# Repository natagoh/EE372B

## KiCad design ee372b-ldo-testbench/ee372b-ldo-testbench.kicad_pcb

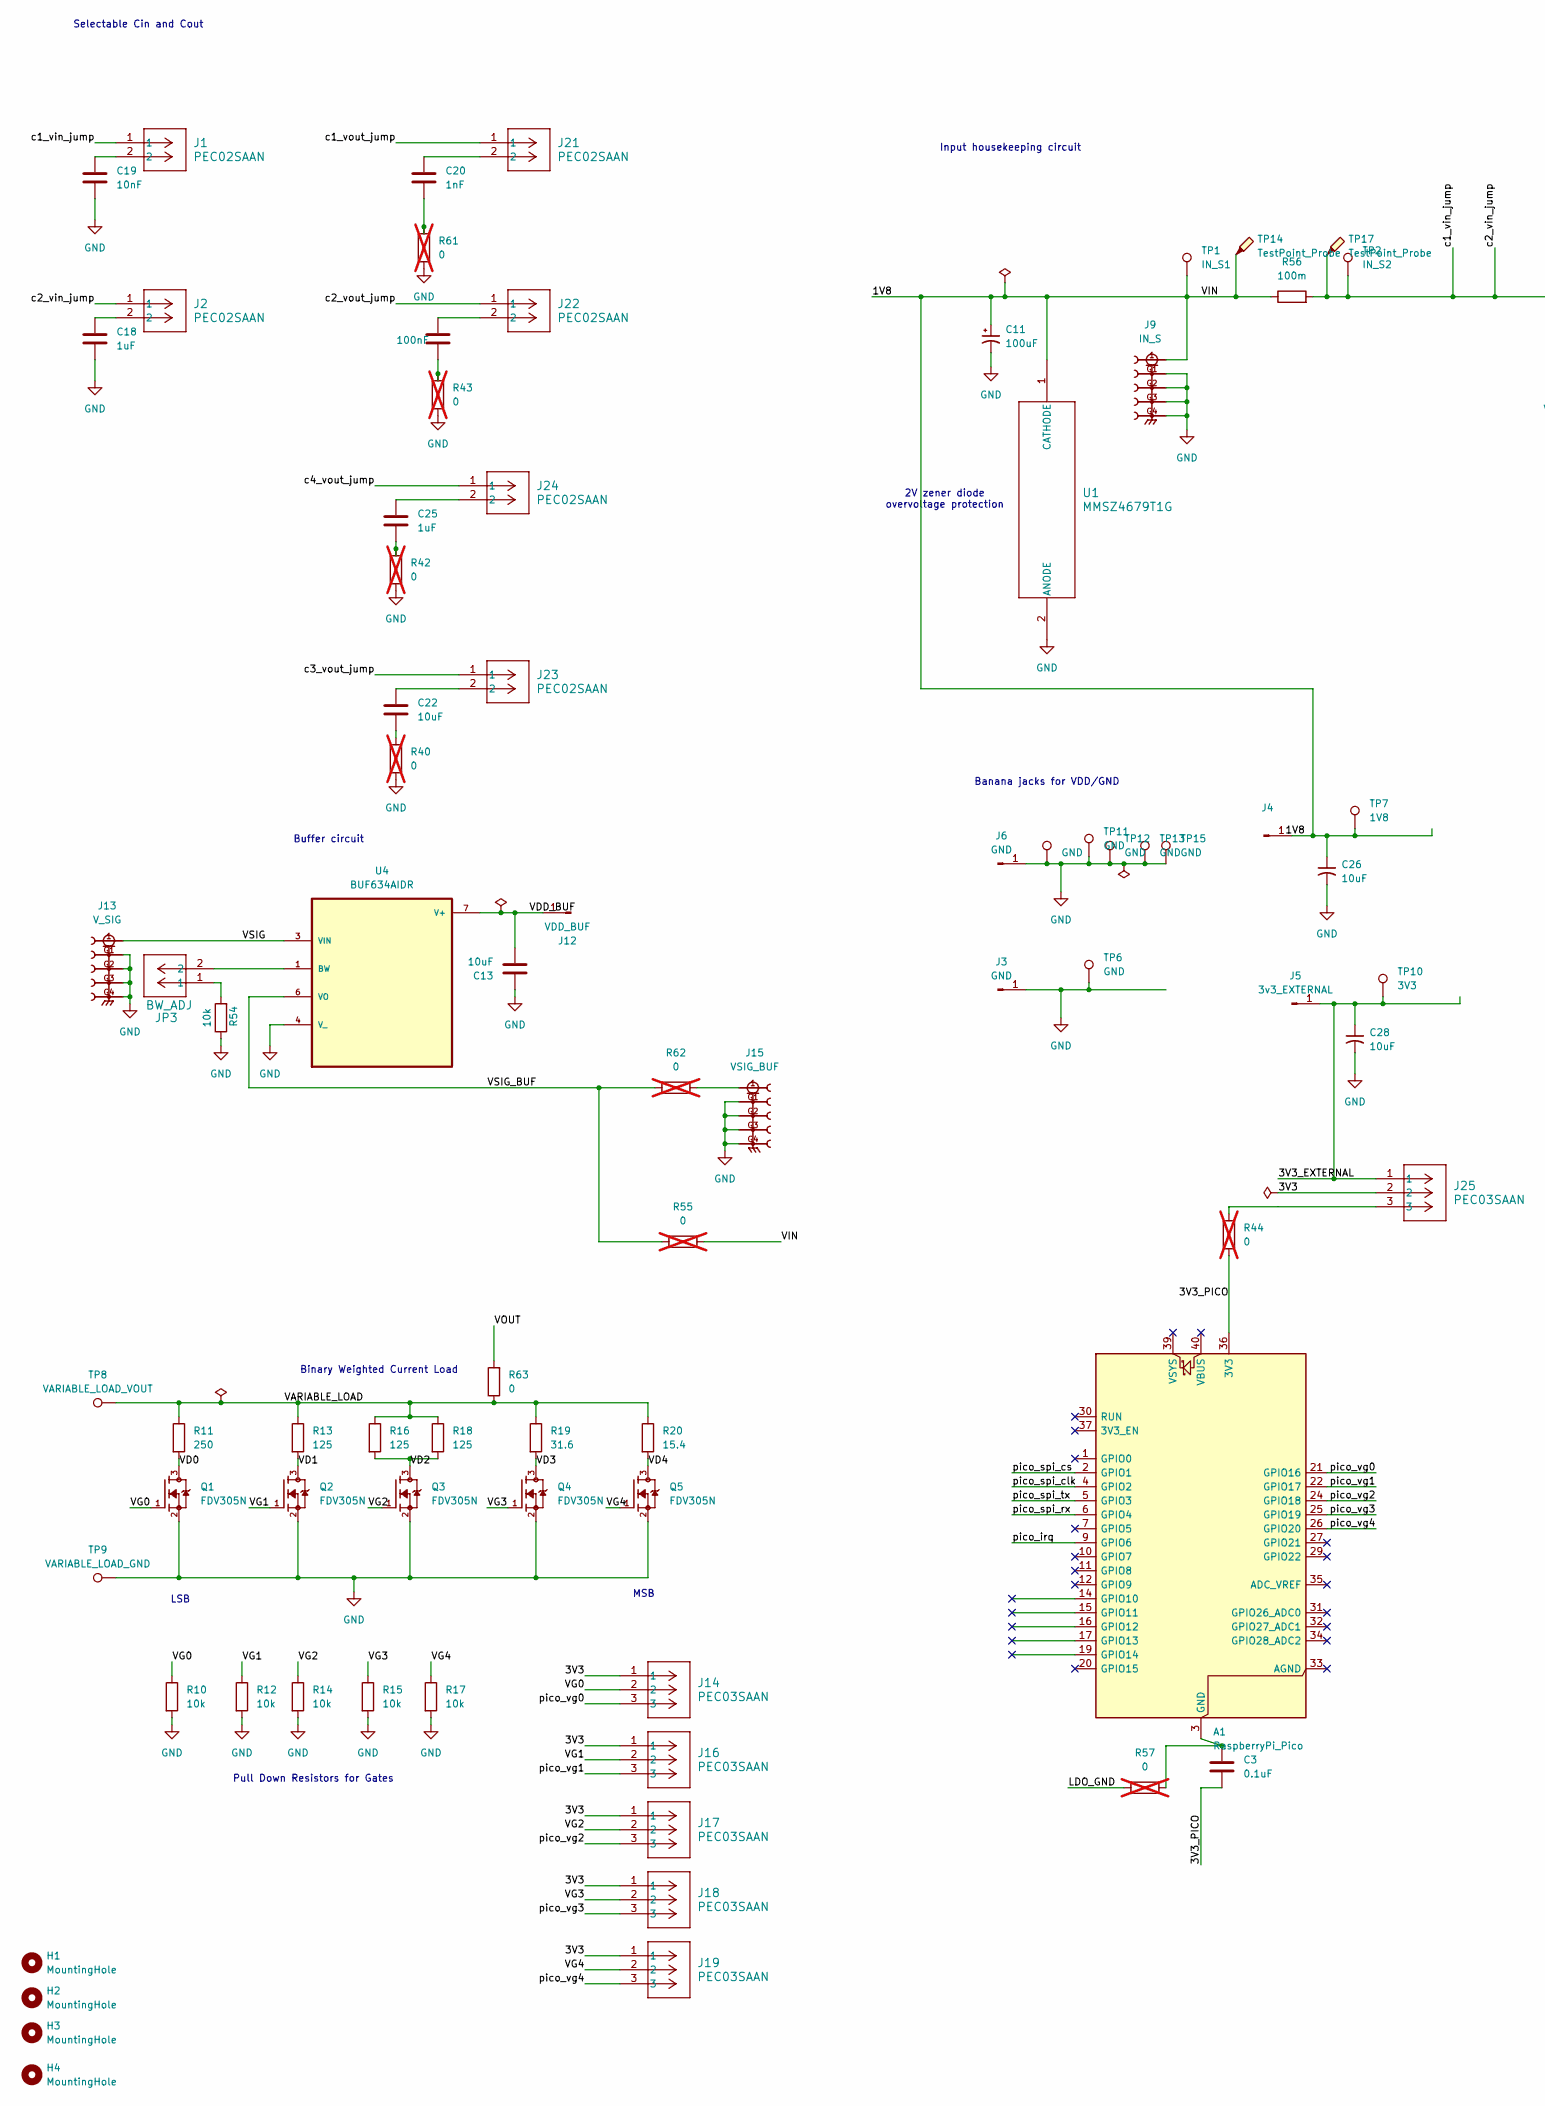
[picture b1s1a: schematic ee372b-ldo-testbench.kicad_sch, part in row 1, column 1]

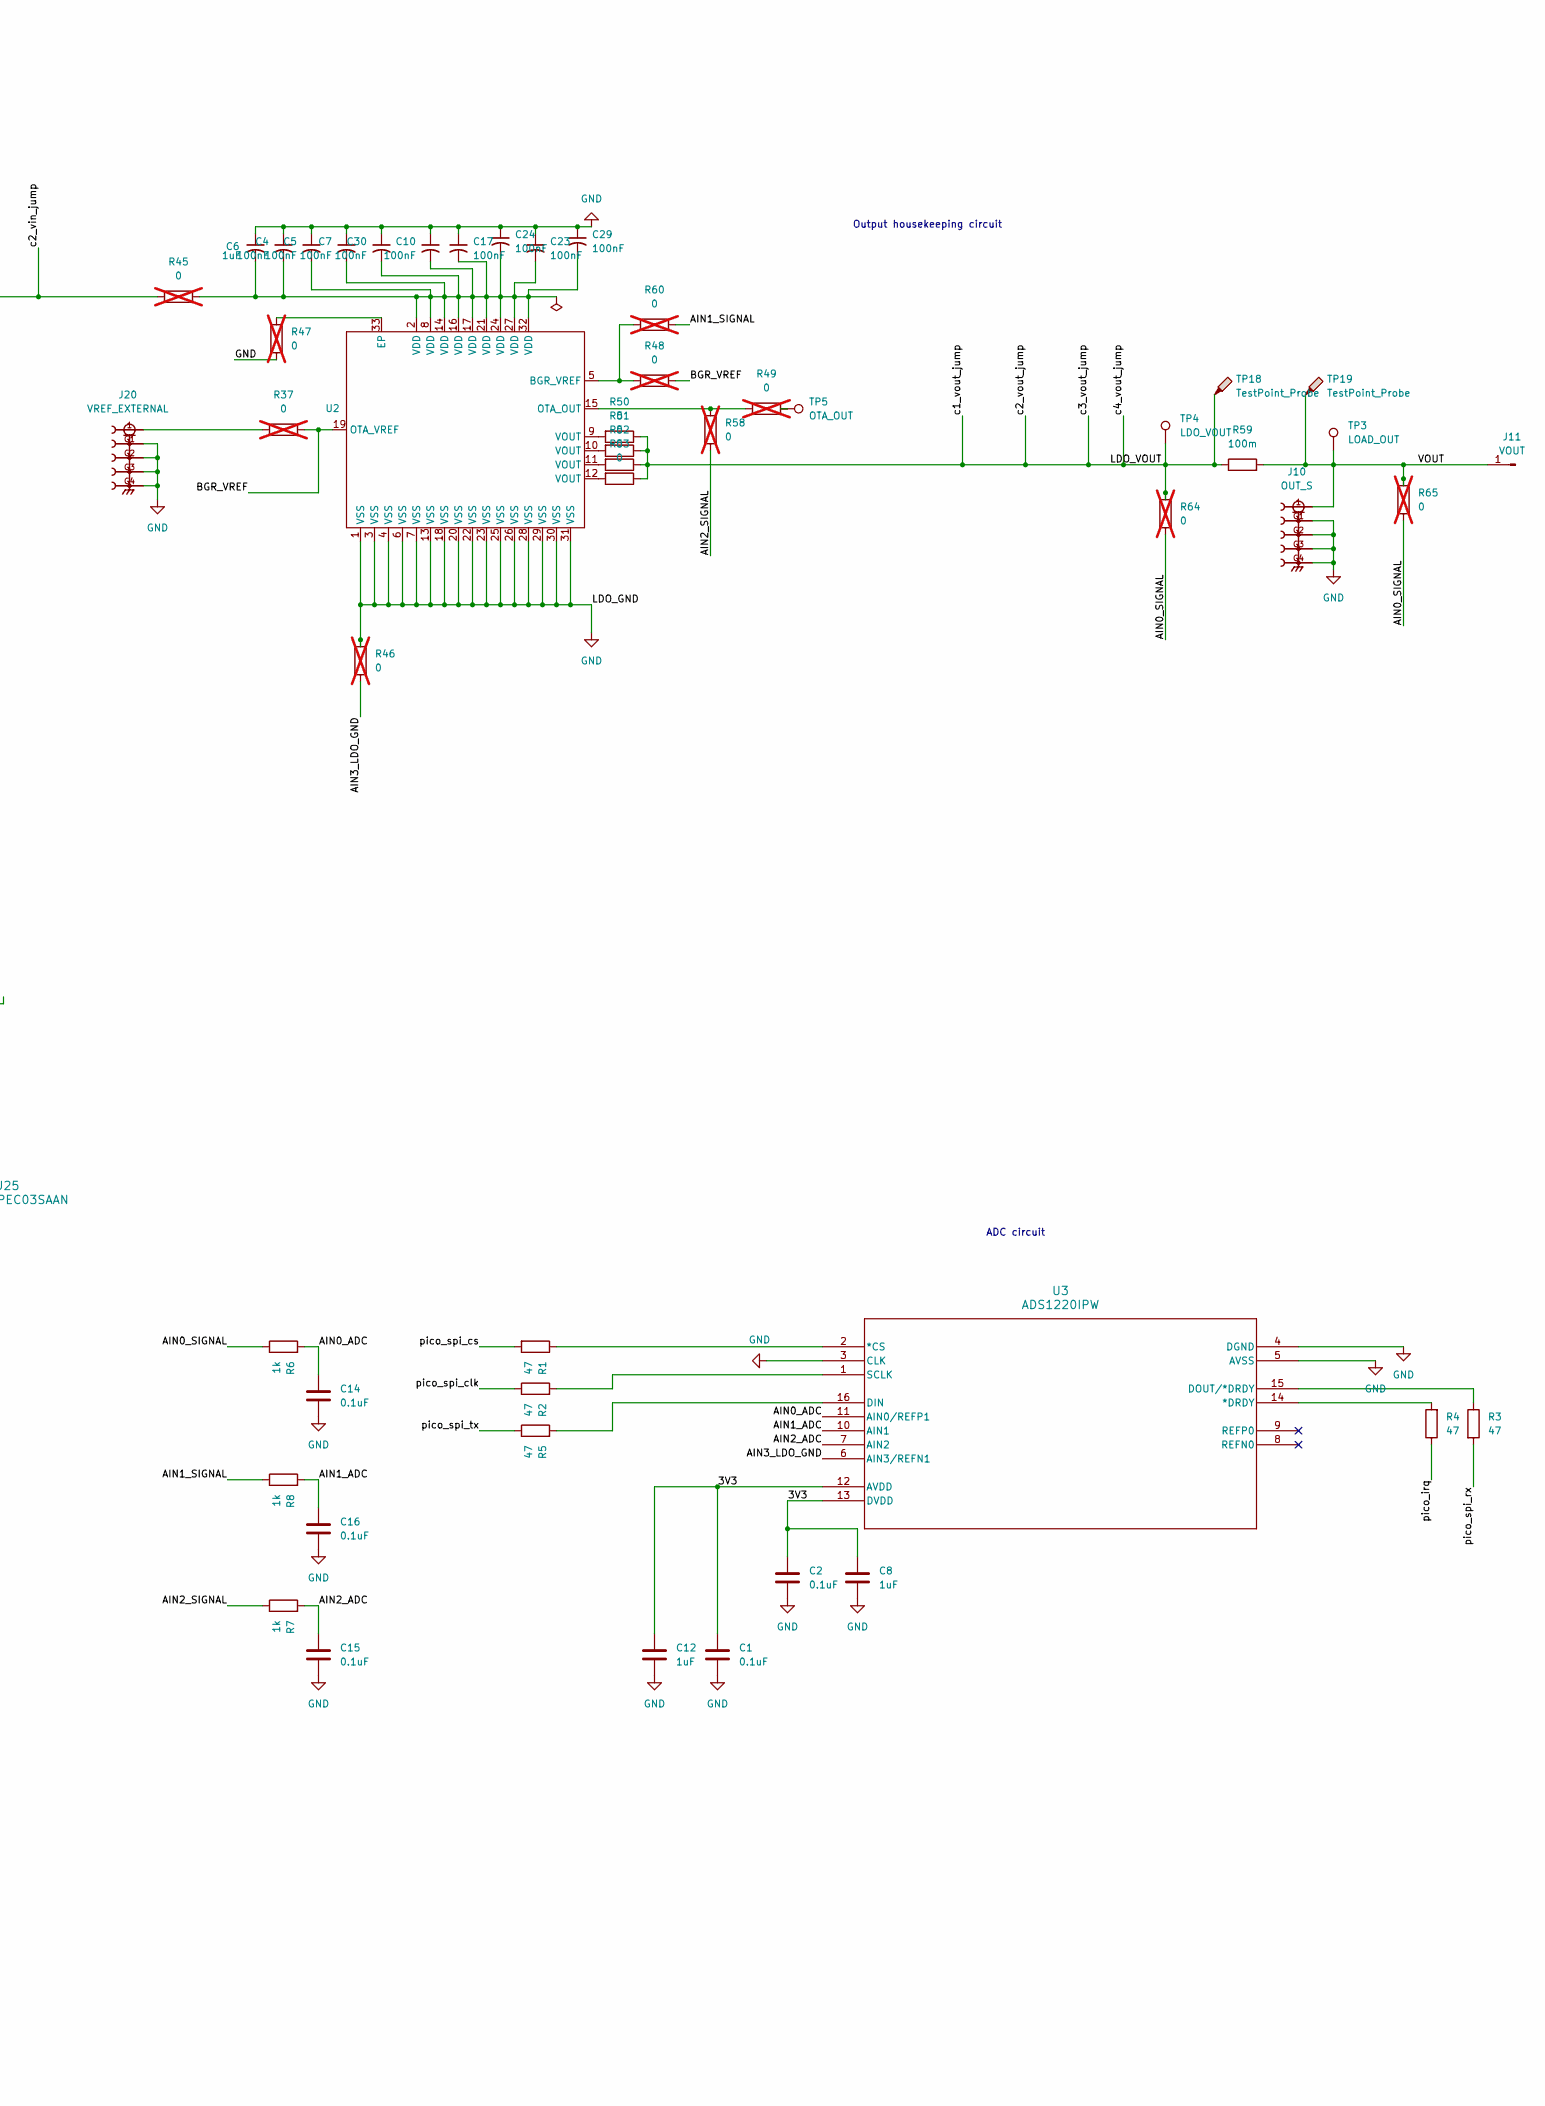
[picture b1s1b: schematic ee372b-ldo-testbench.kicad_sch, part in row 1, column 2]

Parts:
A1: RaspberryPi_Pico; RaspberryPi_Pico_Common_Unspecified
C1, C2, C3, C14, C15, C16: 0.1uF; C_0805_2012Metric_Pad1.18x1.45mm_HandSolder
C4, C5, C7, C10, C17, C23, C24, C29, C30: 100nF; C_0805_2012Metric_Pad1.18x1.45mm_HandSolder
C6, C8, C12: 1uF; C_0805_2012Metric_Pad1.18x1.45mm_HandSolder
C11: 100uF; CAPPRD350W60D800H1150; Manufacturer Part Number EEU-FC1V101
C13, C22: 10uF; C_0805_2012Metric_Pad1.18x1.45mm_HandSolder; Manufacturer Part Number C0805C106K8RACTU
C18, C25: 1uF; C_0805_2012Metric_Pad1.18x1.45mm_HandSolder; Manufacturer Part Number C0805C104K8RACTU
C19: 10nF; C_0805_2012Metric_Pad1.18x1.45mm_HandSolder; Manufacturer Part Number C0805C101K8RACTU
C20: 1nF; C_0805_2012Metric_Pad1.18x1.45mm_HandSolder; Manufacturer Part Number C0805C101K8RACTU
C21: 100nF; C_0805_2012Metric_Pad1.18x1.45mm_HandSolder; Manufacturer Part Number C0805C104K8RACTU
C26, C28: 10uF; C_0805_2012Metric_Pad1.18x1.45mm_HandSolder
H1, H2, H3, H4: MountingHole; MountingHole_2.5mm
J1, J2, J21, J22, J23, J24: PEC02SAAN; CONN_PxC02S_SUL
J3, J6: GND; CALTEST_CT3151-2; Manufacturer Part Number CT3151SP-0
J4: 1V8; CALTEST_CT3151-2; Manufacturer Part Number CT3151SP-0
J5: 3v3_EXTERNAL; CALTEST_CT3151-2; Manufacturer Part Number CT3151SP-0
J9: IN_S; SAMTEC_SMA-J-P-H-ST-TH1; Manufacturer Part Number SMA-J-P-H-ST-TH1
J10: OUT_S; SAMTEC_SMA-J-P-H-ST-TH1; Manufacturer Part Number SMA-J-P-H-ST-TH1
J11: VOUT; CALTEST_CT3151-2; Manufacturer Part Number CT3151SP-6
J12: VDD_BUF; CALTEST_CT3151-2; Manufacturer Part Number CT3151SP-2
J13: V_SIG; SAMTEC_SMA-J-P-H-ST-TH1; Manufacturer Part Number SMA-J-P-H-ST-TH1
J14, J16, J17, J18, J19, J25: PEC03SAAN; CONN_PEC03SAAN_SUL
J15: VSIG_BUF; SAMTEC_SMA-J-P-H-ST-TH1; Manufacturer Part Number SMA-J-P-H-ST-TH1
J20: VREF_EXTERNAL; SAMTEC_SMA-J-P-H-ST-TH1; Manufacturer Part Number SMA-J-P-H-ST-TH1
JP3: BW_ADJ; CONN_PxC02S_SUL; Manufacturer Part Number PEC02SAAN
Q1, Q2, Q3, Q4, Q5: FDV305N; SOT95P240X111-3N; Manufacturer Part Number FDV305N
R1, R2, R3, R4, R5: 47; R_0805_2012Metric_Pad1.20x1.40mm_HandSolder
R6, R7, R8: 1k; R_0805_2012Metric_Pad1.20x1.40mm_HandSolder
R10, R12, R14, R15, R17, R54: 10k; R_0805_2012Metric_Pad1.20x1.40mm_HandSolder; Manufacturer Part Number RC0805FR-0710KL
R11: 250; R_0805_2012Metric_Pad1.20x1.40mm_HandSolder; Manufacturer Part Number RQ73C2A249RBTD
R13, R16, R18: 125; R_0805_2012Metric_Pad1.20x1.40mm_HandSolder; Manufacturer Part Number RQ73C2A124RBTD
R19: 31.6; R_0805_2012Metric_Pad1.20x1.40mm_HandSolder; Manufacturer Part Number RQ73C2A31R6BTD
R20: 15.4; R_0805_2012Metric_Pad1.20x1.40mm_HandSolder; Manufacturer Part Number RQ73C2A15R4BTDF
R37, R40, R42, R43, R44, R45, R46, R47, R48, R49, R58, R60, R61, R64, R65: 0; R_0805_2012Metric_Pad1.20x1.40mm_HandSolder; not fitted
R50, R51, R52, R53: 0; R_0805_2012Metric_Pad1.20x1.40mm_HandSolder
R55, R57, R62: 0; R_0805_2012Metric_Pad1.20x1.40mm_HandSolder; Manufacturer Part Number CRCW08050000Z0EAHP; not fitted
R56, R59: 100m; R_2512_6332Metric_Pad1.40x3.35mm_HandSolder; Manufacturer Part Number PA2512FKE7W0R1E
R63: 0; R_0805_2012Metric_Pad1.20x1.40mm_HandSolder; Manufacturer Part Number CRCW08050000Z0EAHP
TP1: IN_S1; KEYSTONE_5016; Manufacturer Part Number 5016
TP2: IN_S2; KEYSTONE_5016; Manufacturer Part Number 5016
TP3: LOAD_OUT; KEYSTONE_5016; Manufacturer Part Number 5016
TP4: LDO_VOUT; KEYSTONE_5016; Manufacturer Part Number 5016
TP5: OTA_OUT; KEYSTONE_5016; Manufacturer Part Number 5016
TP6, TP11, TP12, TP13, TP15, TP16: GND; KEYSTONE_5016; Manufacturer Part Number 5016
TP7: 1V8; KEYSTONE_5016; Manufacturer Part Number 5016
TP8: VARIABLE_LOAD_VOUT; KEYSTONE_5016; Manufacturer Part Number 5016
TP9: VARIABLE_LOAD_GND; KEYSTONE_5016; Manufacturer Part Number 5016
TP10: 3V3; KEYSTONE_5016; Manufacturer Part Number 5016
TP14, TP17, TP18, TP19: TestPoint_Probe; TestPoint_Pad_D1.0mm
U1: MMSZ4679T1G; SOD-123_ONS
U2: QFN-32_EP_7x7_Pitch0.65mm
U3: ADS1220IPW; PW16
U4: BUF634AIDR; SOIC127P599X175-8N; Manufacturer Part Number BUF634AIDR

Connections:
/3V3: C1.1, C2.1, C8.1, C12.1, J14.1, J16.1, J17.1, J18.1, J19.1, J25.2, U3.12 (AVDD), U3.13 (DVDD)
/3V3_EXTERNAL: C28.1, J5.1 (Pin_1_1), J25.1, TP10.1 (1_1)
/3V3_PICO: A1.36 (3V3), C3.2, R44.2
/AIN0_ADC: C14.1, R6.2, U3.11 (AIN0/REFP1)
/AIN0_SIGNAL: R6.1, R64.1, R65.1
/AIN1_ADC: C16.1, R8.2, U3.10 (AIN1)
/AIN1_SIGNAL: R8.1, R60.1
/AIN2_ADC: C15.1, R7.2, U3.7 (AIN2)
/AIN2_SIGNAL: R7.1, R58.1
/AIN3_LDO_GND: R46.1, U3.6 (AIN3/REFN1)
/BGR_VREF: R37.2, R48.1, U2.19 (OTA_VREF)
/LDO_VOUT: J21.1, J22.1, J23.1, J24.1, R50.1, R51.1, R52.1, R53.1, R59.1, R64.2, TP4.1 (1_1), TP18.1 (1_1)
/VARIABLE_LOAD: R11.1, R13.1, R16.1, R18.1, R19.1, R20.1, R63.1, TP8.1 (1_1)
/VD0: Q1.3, R11.2
/VD1: Q2.3, R13.2
/VD2: Q3.3, R16.2, R18.2
/VD3: Q4.3, R19.2
/VD4: Q5.3, R20.2
/VDD_BUF: C13.2, J12.1 (Pin_1_1), U4.7 (V+)
/VG0: J14.2, Q1.1, R10.1
/VG1: J16.2, Q2.1, R12.1
/VG2: J17.2, Q3.1, R14.1
/VG3: J18.2, Q4.1, R15.1
/VG4: J19.2, Q5.1, R17.1
/VOUT: J10.1, J11.1 (Pin_1_1), R59.2, R63.2, R65.2, TP3.1 (1_1), TP19.1 (1_1)
/VSIG: J13.1, U4.3 (VIN)
/VSIG_BUF: R55.1, R62.1, U4.6 (VO)
/c1_vin_jump: J1.1, J2.1, R45.1, R56.2, TP2.1 (1_1), TP17.1 (1_1)
/pico_irq: A1.9 (GPIO6), R4.1
/pico_spi_clk: A1.4 (GPIO2), R2.1
/pico_spi_cs: A1.2 (GPIO1), R1.2
/pico_spi_rx: A1.6 (GPIO4), R3.2
/pico_spi_tx: A1.5 (GPIO3), R5.1
/pico_vg0: A1.21 (GPIO16), J14.3
/pico_vg1: A1.22 (GPIO17), J16.3
/pico_vg2: A1.24 (GPIO18), J17.3
/pico_vg3: A1.25 (GPIO19), J18.3
/pico_vg4: A1.26 (GPIO20), J19.3
GND: C1.2, C2.2, C4.1, C5.1, C6.1, C7.1, C8.2, C10.1, C11.N, C12.2, C13.1, C14.2, C15.2, C16.2, C17.1, C18.2, C19.2, C23.1, C24.1, C26.2, C28.2, C29.1, C30.1, J3.1 (Pin_1_1), J6.1 (Pin_1_1), J9.G1, J9.G2, J9.G3, J9.G4, J10.G1, J10.G2, J10.G3, J10.G4, J13.G1, J13.G2, J13.G3, J13.G4, J15.G1, J15.G2, J15.G3, J15.G4, J20.G1, J20.G2, J20.G3, J20.G4, Q1.2, Q2.2, Q3.2, Q4.2, Q5.2, R10.2, R12.2, R14.2, R15.2, R17.2, R40.1, R42.1, R43.1, R46.2, R47.1, R54.1, R57.1, R61.1, TP6.1 (1_1), TP9.1 (1_1), TP11.1 (1_1), TP12.1 (1_1), TP13.1 (1_1), TP15.1 (1_1), TP16.1, U1.2 (ANODE), U2.1 (VSS), U2.3 (VSS), U2.4 (VSS), U2.6 (VSS), U2.7 (VSS), U2.13 (VSS), U2.18 (VSS), U2.20 (VSS), U2.22 (VSS), U2.23 (VSS), U2.25 (VSS), U2.26 (VSS), U2.28 (VSS), U2.29 (VSS), U2.30 (VSS), U2.31 (VSS), U3.3 (CLK), U3.4 (DGND), U3.5 (AVSS), U4.4 (V_); also elsewhere on the board
unnamed: A1.3 (GND), A1.8 (GND), A1.13 (GND), A1.18 (GND), A1.23 (GND), A1.28 (GND), A1.38 (GND), C3.1, R57.2
unnamed: C4.2, C5.2, C6.2, C7.2, C10.2, C17.2, C23.2, C24.2, C29.2, C30.2, R45.2, U2.2 (VDD), U2.8 (VDD), U2.14 (VDD), U2.16 (VDD), U2.17 (VDD), U2.21 (VDD), U2.24 (VDD), U2.27 (VDD), U2.32 (VDD)
unnamed: C18.1, J2.2
unnamed: C19.1, J1.2
unnamed: C20.1, J21.2
unnamed: C20.2, R61.2
unnamed: C21.1, J22.2
unnamed: C21.2, R43.2
unnamed: C22.1, J23.2
unnamed: C22.2, R40.2
unnamed: C25.1, J24.2
unnamed: C25.2, R42.2
unnamed: J15.1, R62.2
unnamed: J20.1, R37.1
unnamed: J25.3, R44.1
unnamed: JP3.1, R54.2
unnamed: R49.1, TP5.1 (1_1)
unnamed: R50.2, U2.9 (VOUT)
unnamed: R51.2, U2.10 (VOUT)
unnamed: R52.2, U2.11 (VOUT)
unnamed: R53.2, U2.12 (VOUT)
unnamed: R48.2, R60.2, U2.5 (BGR_VREF)
unnamed: R47.2, U2.33 (EP)
unnamed: R49.2, R58.2, U2.15 (OTA_OUT)
unnamed: R1.1, U3.2 (*CS)
unnamed: R4.2, U3.14 (*DRDY)
unnamed: R5.2, U3.16 (DIN)
unnamed: R3.1, U3.15 (DOUT/*DRDY)
unnamed: R2.2, U3.1 (SCLK)
unnamed: JP3.2, U4.1 (BW)

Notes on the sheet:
LSB
Banana jacks for VDD/GND
Binary Weighted Current Load
Selectable Cin and Cout
Pull Down Resistors for Gates
2V zener diode overvoltage protection
Input housekeeping circuit
MSB
Output housekeeping circuit
Buffer circuit
ADC circuit

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
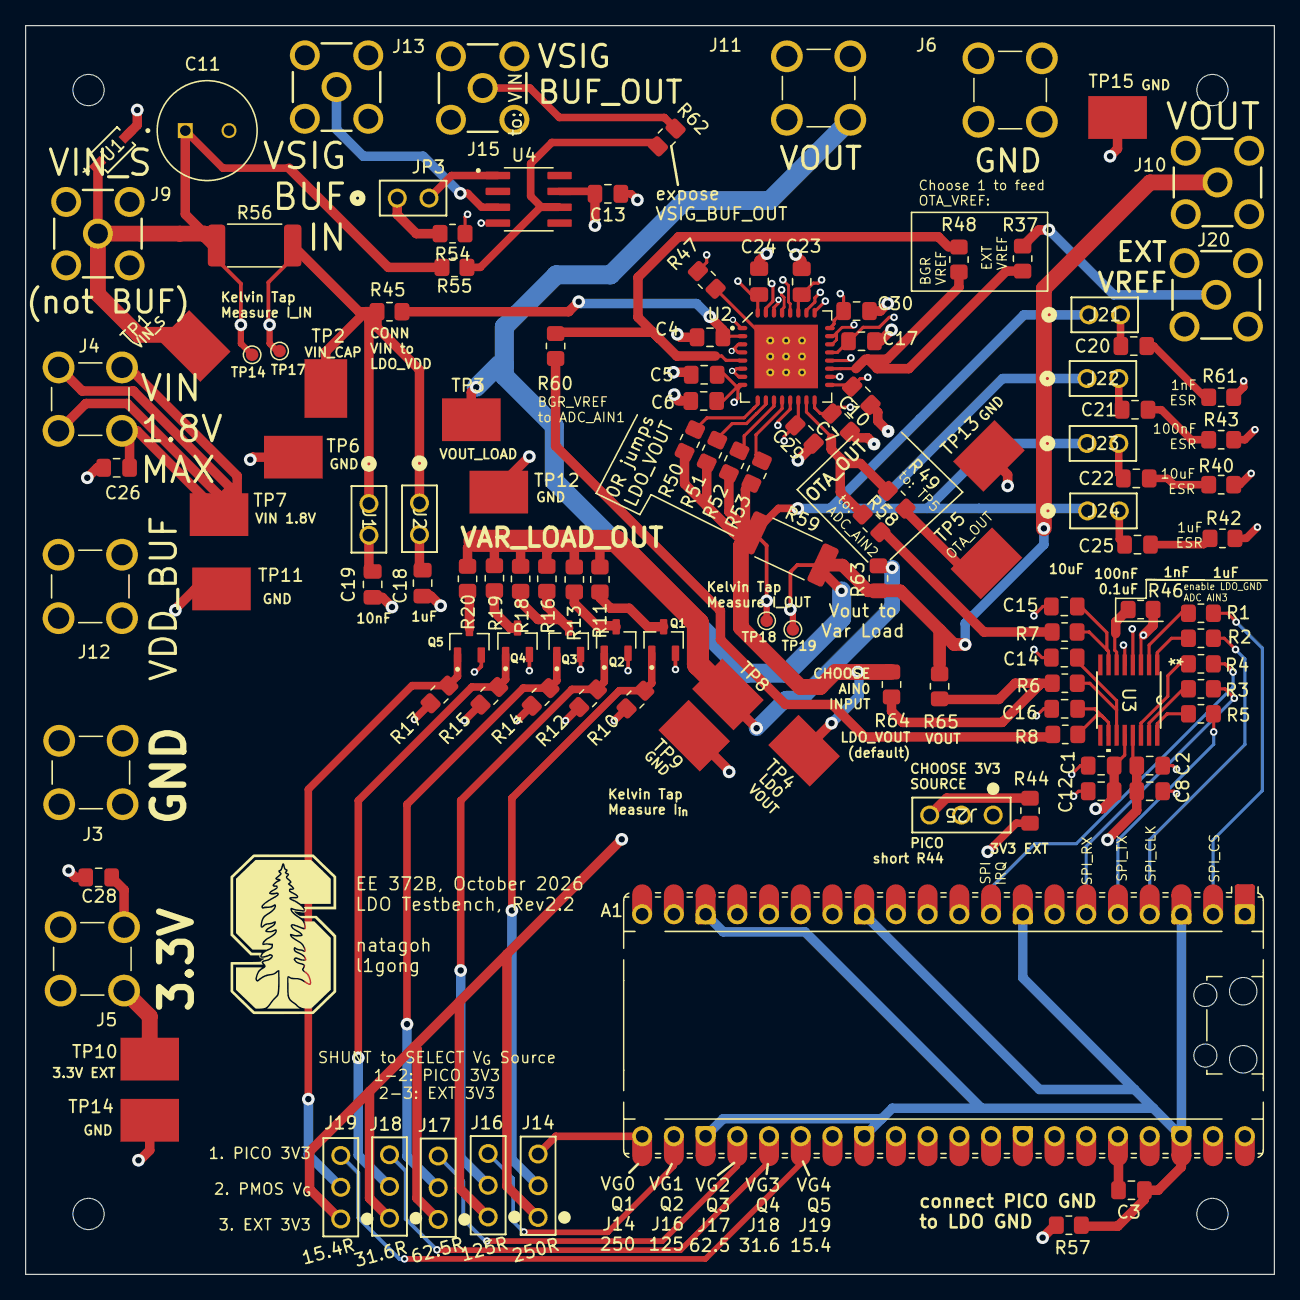
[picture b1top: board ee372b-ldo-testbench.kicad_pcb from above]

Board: 4 copper layers, 100.0 x 100.0 mm, 130 parts (0 on the bottom side), 71 nets.

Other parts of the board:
TP14#2: GND; KEYSTONE_5016

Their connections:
GND: TP14#2.1 (1_1); also elsewhere on the board
